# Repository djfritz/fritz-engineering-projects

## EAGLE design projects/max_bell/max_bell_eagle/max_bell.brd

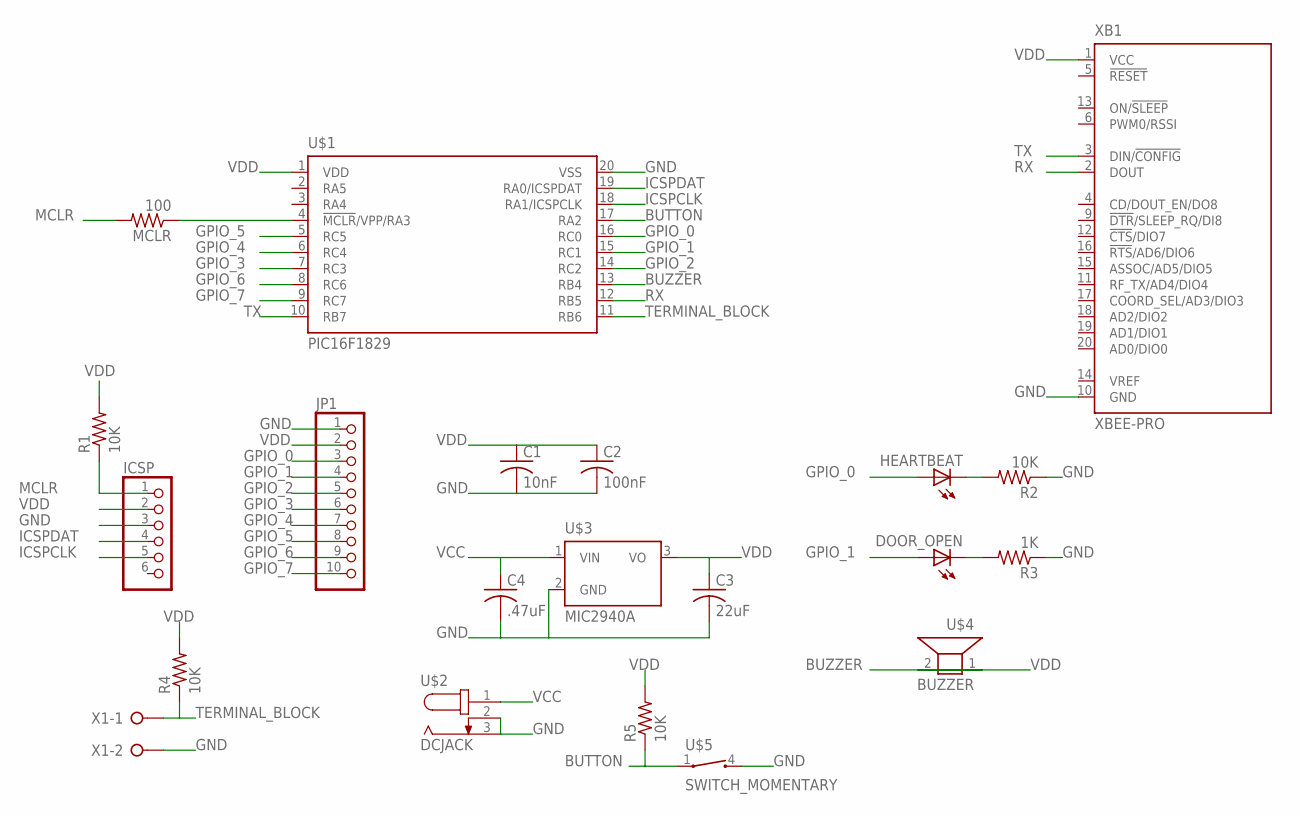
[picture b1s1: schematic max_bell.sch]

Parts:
C1: 10nF; C050-035X075
C2: 100nF; C050-035X075
C3: 22uF; C050-035X075
C4: .47uF; C050-035X075
DOOR_OPEN: LED5MM
HEARTBEAT: LED5MM
ICSP: PINHD-1X6; 1X06
JP1: PINHD-1X10; 1X10
MCLR: 100; 0309/12
R1, R2, R4, R5: 10K; 0309/12
R3: 1K; 0309/12
U$1: PIC16F1829; DIL20
U$2: DCJACK; DCJACKFP
U$3: MIC2940A; TO220V
U$4: BUZZER
U$5: SWITCH_MOMENTARY; MOMENTARY_SWITCH
X1: W237-02P; W237-132
XB1: XBEE-PRO

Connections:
BUTTON: R5.1, U$1.17 (RA2), U$5.1
BUZZER: U$1.13 (RB4), U$4.1
GND: C1.2, C2.2, C3.2, C4.2, ICSP.3, JP1.1, R2.1, R3.1, U$1.20 (VSS), U$2.2, U$2.3 (1), U$3.2 (GND), U$5.4 (2), X1.2, XB1.10 (GND)
GPIO_0: HEARTBEAT.A, JP1.3, U$1.16 (RC0)
GPIO_1: DOOR_OPEN.A, JP1.4, U$1.15 (RC1)
GPIO_2: JP1.5, U$1.14 (RC2)
GPIO_3: JP1.6, U$1.7 (RC3)
GPIO_4: JP1.7, U$1.6 (RC4)
GPIO_5: JP1.8, U$1.5 (RC5)
GPIO_6: JP1.9, U$1.8 (RC6)
GPIO_7: JP1.10, U$1.9 (RC7)
ICSPCLK: ICSP.5, U$1.18 (RA1/ICSPCLK)
ICSPDAT: ICSP.4, U$1.19 (RA0/ICSPDAT)
MCLR: ICSP.1, MCLR.2, R1.1
unnamed: MCLR.1, U$1.4 (!MCLR!/VPP/RA3)
unnamed: HEARTBEAT.K (C), R2.2
unnamed: DOOR_OPEN.K (C), R3.2
RX: U$1.12 (RB5), XB1.2 (DOUT)
TERMINAL_BLOCK: R4.1, U$1.11 (RB6), X1.1
TX: U$1.10 (RB7), XB1.3 (DIN/!CONFIG)
VCC: C4.1, U$2.1 (3), U$3.1 (VIN)
VDD: C1.1, C2.1, C3.1, ICSP.2, JP1.2, R1.2, R4.2, R5.2, U$1.1 (VDD), U$3.3 (VO), U$4.2, XB1.1 (VCC)

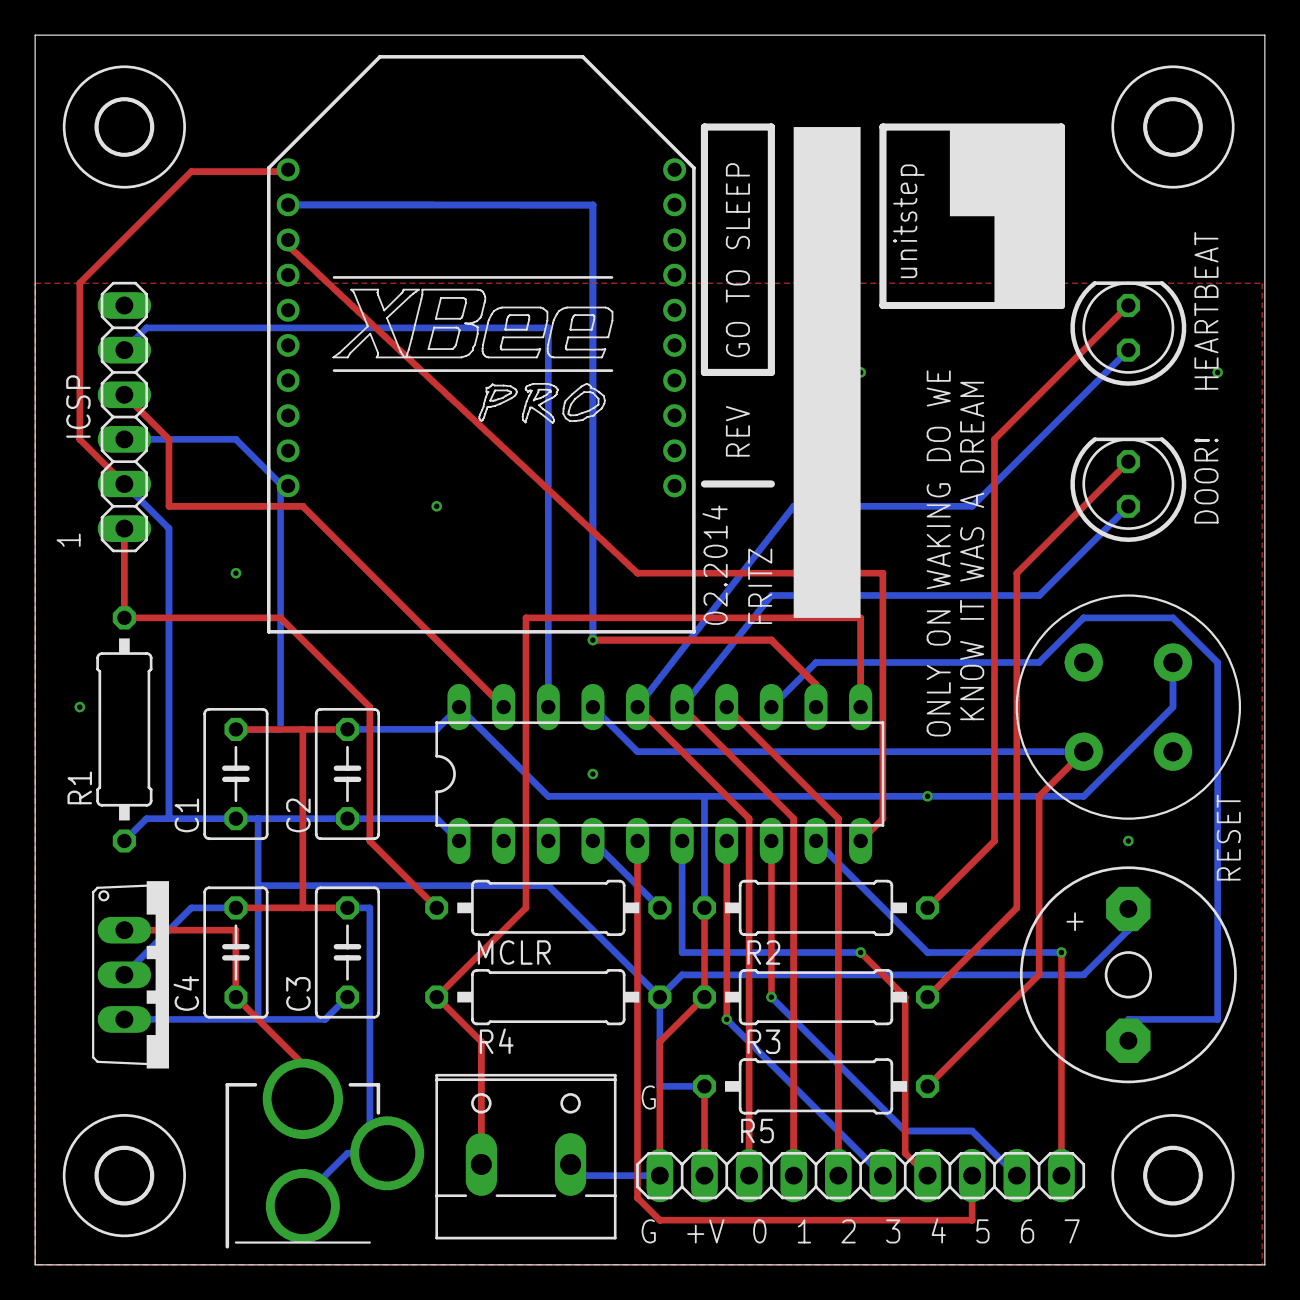
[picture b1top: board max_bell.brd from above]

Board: 2 copper layers, 70.0 x 70.0 mm, 25 parts (0 on the bottom side), 22 nets.

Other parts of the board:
U$6, U$7, U$8, U$9: 3,0

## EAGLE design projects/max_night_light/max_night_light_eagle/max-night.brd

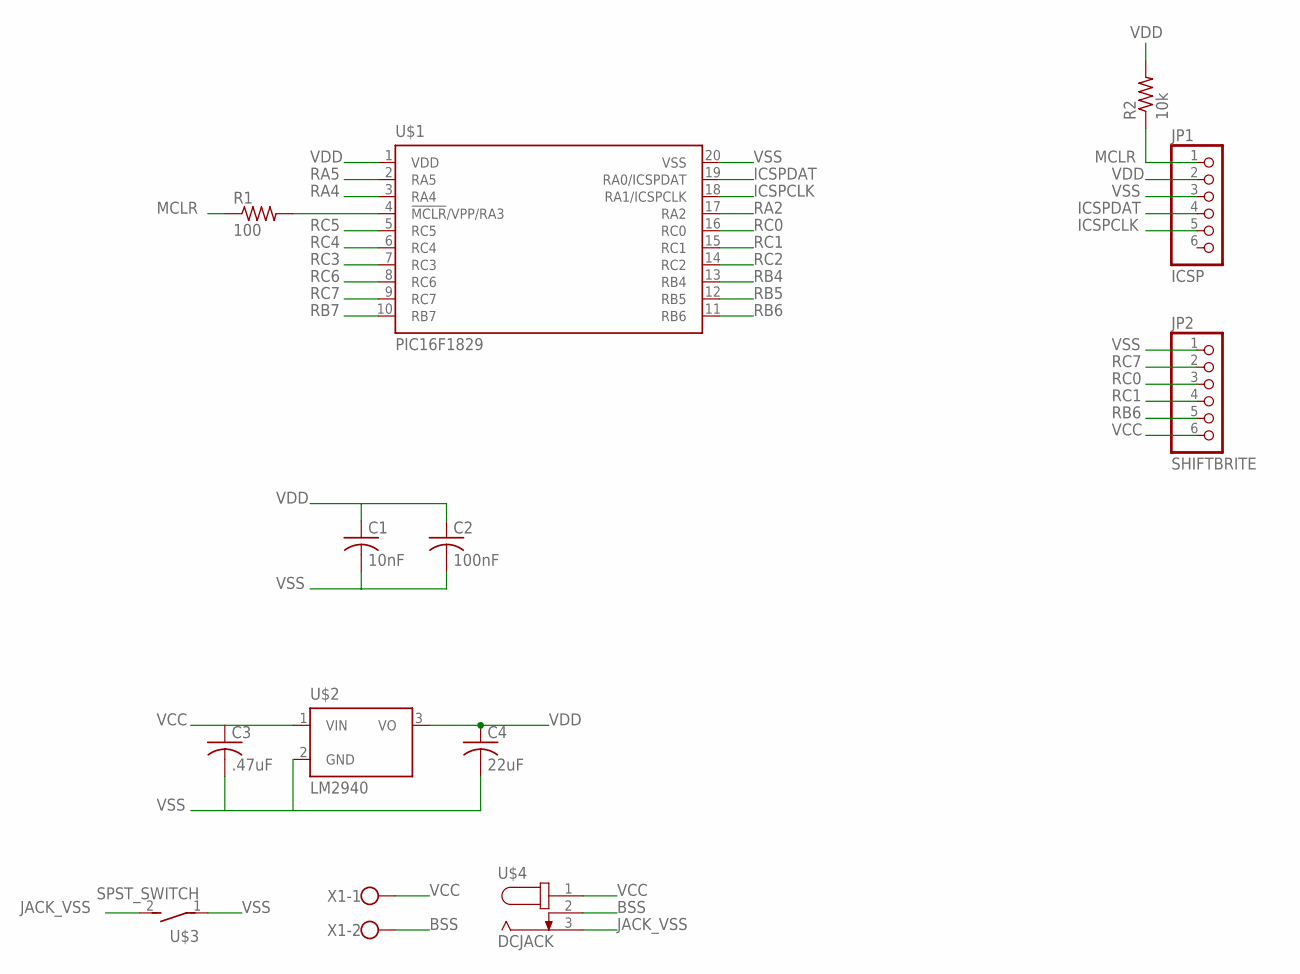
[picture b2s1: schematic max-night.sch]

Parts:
C1: 10nF; C050-035X075
C2: 100nF; C050-035X075
C3: .47uF; C050-035X075
C4: 22uF; C050-035X075
JP1: ICSP; 1X06
JP2: SHIFTBRITE; 1X06
R1: 100; 0309/12
R2: 10k; 0309/12
U$1: PIC16F1829; DIL20
U$2: LM2940; TO220V
U$3: SPST_SWITCH; SWITCH_SPST
U$4: DCJACK; DCJACKFP
X1: W237-102

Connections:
BSS: U$4.2, X1.2
ICSPCLK: JP1.5, U$1.18 (RA1/ICSPCLK)
ICSPDAT: JP1.4, U$1.19 (RA0/ICSPDAT)
JACK_VSS: U$3.2 (S), U$4.3 (1)
MCLR: JP1.1, R1.1, R2.1
unnamed: R1.2, U$1.4 (!MCLR!/VPP/RA3)
RA2: U$1.17 (RA2)
RA4: U$1.3 (RA4)
RA5: U$1.2 (RA5)
RB4: U$1.13 (RB4)
RB5: U$1.12 (RB5)
RB6: JP2.5, U$1.11 (RB6)
RB7: U$1.10 (RB7)
RC0: JP2.3, U$1.16 (RC0)
RC1: JP2.4, U$1.15 (RC1)
RC2: U$1.14 (RC2)
RC3: U$1.7 (RC3)
RC4: U$1.6 (RC4)
RC5: U$1.5 (RC5)
RC6: U$1.8 (RC6)
RC7: JP2.2, U$1.9 (RC7)
VCC: C3.1, JP2.6, U$2.1 (VIN), U$4.1 (3), X1.1
VDD: C1.1, C2.1, C4.1, JP1.2, R2.2, U$1.1 (VDD), U$2.3 (VO)
VSS: C1.2, C2.2, C3.2, C4.2, JP1.3, JP2.1, U$1.20 (VSS), U$2.2 (GND), U$3.1

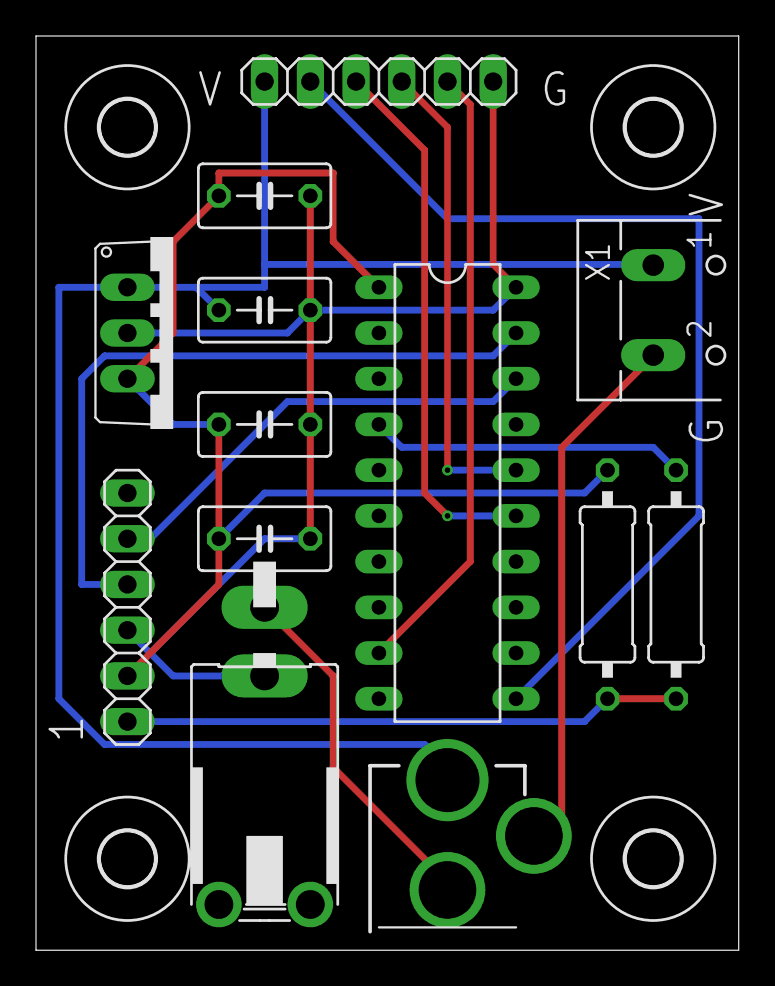
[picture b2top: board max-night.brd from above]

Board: 2 copper layers, 39.0 x 50.8 mm, 17 parts (0 on the bottom side), 13 nets.

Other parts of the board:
U$5, U$6, U$7, U$8: 3,0

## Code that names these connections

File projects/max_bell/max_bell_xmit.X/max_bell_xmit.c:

/*
 * File:   main.c
 * Author: fritz
 *
 */

// PIC16F1829 Configuration Bit Settings

#include <xc.h>

// #pragma config statements should precede project file includes.
// Use project enums instead of #define for ON and OFF.

// CONFIG1
#pragma config FOSC = INTOSC    // Oscillator Selection (INTOSC oscillator: I/O function on CLKIN pin)
#pragma config WDTE = OFF       // Watchdog Timer Enable (WDT disabled)
#pragma config PWRTE = OFF      // Power-up Timer Enable (PWRT disabled)
#pragma config MCLRE = ON       // MCLR Pin Function Select (MCLR/VPP pin function is MCLR)
#pragma config CP = OFF         // Flash Program Memory Code Protection (Program memory code protection is disabled)
#pragma config CPD = OFF        // Data Memory Code Protection (Data memory code protection is disabled)
#pragma config BOREN = OFF       // Brown-out Reset Enable (Brown-out Reset enabled)
#pragma config CLKOUTEN = OFF   // Clock Out Enable (CLKOUT function is disabled. I/O or oscillator function on the CLKOUT pin)
#pragma config IESO = OFF        // Internal/External Switchover (Internal/External Switchover mode is enabled)
#pragma config FCMEN = OFF       // Fail-Safe Clock Monitor Enable (Fail-Safe Clock Monitor is enabled)

// CONFIG2
#pragma config WRT = OFF        // Flash Memory Self-Write Protection (Write protection off)
#pragma config PLLEN = OFF       // PLL Enable (4x PLL enabled)
#pragma config STVREN = ON      // Stack Overflow/Underflow Reset Enable (Stack Overflow or Underflow will cause a Reset)
#pragma config BORV = LO        // Brown-out Reset Voltage Selection (Brown-out Reset Voltage (Vbor), low trip point selected.)
#pragma config LVP = OFF        // Low-Voltage Programming Enable (High-voltage on MCLR/VPP must be used for programming)

#include <stdio.h>
#include <stdlib.h>

#define _XTAL_FREQ 500000 /* 500kHz default intosc */
#define BUZZER RB4
#define DOOR RB6
#define LED_HB RC0
#define LED_DOOR RC1

#define TICK 2000

int main(int argc, char** argv) {
    ANSELA=0;
    ANSELB=0;
    ANSELC=0;
    TRISA = 0xff;
    TRISB = 0xef;
    TRISC = 0xfc;

    RXDTSEL = 0;
    TXCKSEL = 0;
    TXEN = 1;
    SYNC = 0;
    SPEN = 1;
    BRG16 = 1;
    BRGH = 1;
    SPBRGH = 0;
    SPBRGL = 12;

    while (1) {
        __delay_ms(TICK);
        while (!TRMT);
        if (DOOR) {
            TXREG = 1;
        } else {
            TXREG = 2;
        }
    }
    return (EXIT_SUCCESS);
}

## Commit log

2014-02-06 add max night light project
2014-02-06 add order history to night light
2014-02-06 add order history to max_bell
2014-02-06 add commonly used parts list
2014-02-07 max bell work
2014-02-08 update max_bell drawing, start mplab firmware
2014-02-08 updates to max_bell firmware, buzzer is now chirping
2014-02-11 updates to max_bell
2014-02-13 max_bell done
2014-02-14 layout is done and ordered
2014-03-06 remove junk
2015-03-12 Migrating wiki contents from Google Code
